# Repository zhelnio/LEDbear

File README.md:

# LEDbear
Just a simple RGB LED toy

**Schematic**

**Board**

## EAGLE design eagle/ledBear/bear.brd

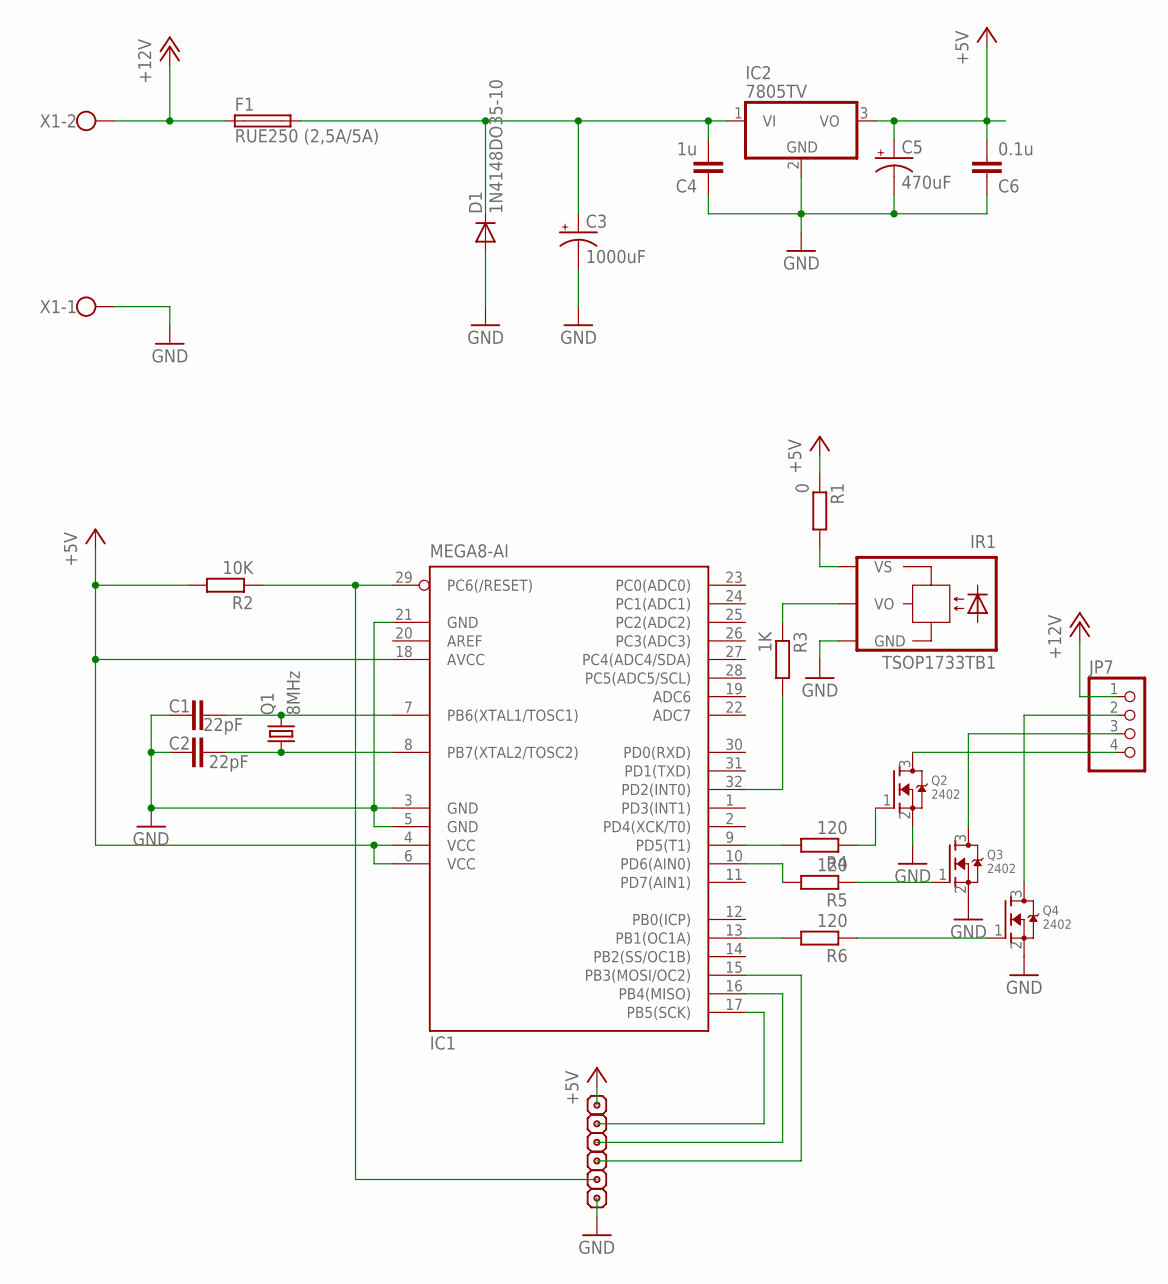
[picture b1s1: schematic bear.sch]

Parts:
C1, C2: 22pF; C1206
C3: 1000uF; E5-10,5
C4: 1u; C1206K
C5: 470uF; E5-8,5
C6: 0.1u; C1206K
D1: 1N4148DO35-10; DO35-10
F1: RUE250 (2,5A/5A); TE5
IC1: MEGA8-AI; TQFP32-08
IC2: 7805TV; TO220V
IR1: TSOP1733TB1; TSOP17_TB1
JP7: PINHD-1X4_2.54; 1X04
JP_5V: PINHD-1X1_2.54; 1X01
JP_GND: PINHD-1X1_2.54; 1X01
JP_MISO: PINHD-1X1_2.54; 1X01
JP_MOSI: PINHD-1X1_2.54; 1X01
JP_RST: PINHD-1X1_2.54; 1X01
JP_SCK: PINHD-1X1_2.54; 1X01
Q1: 8MHz; HC49/S
Q2, Q3, Q4: 2402; SOT23
R1: 0; R1206
R2: 10K; R1206
R3: 1K; R1206
R4, R5, R6: 120; R1206
X1: W237-102

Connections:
+5V: C5.+, C6.2, IC1.4 (VCC), IC1.6 (VCC), IC1.18 (AVCC), IC2.3 (VO), JP_5V.1, R1.1, R2.2
+12V: F1.1, JP7.1, X1.2
GND: C1.1, C2.1, C3.-, C4.1, C5.-, C6.1, D1.A, IC1.3 (GND), IC1.5 (GND), IC1.21 (GND), IC2.2 (GND), IR1.GND, JP_GND.1, Q2.2 (S), Q3.2 (S), Q4.2 (S), X1.1
unnamed: IC1.32 (PD2(INT0)), R3.2
unnamed: IR1.VO, R3.1
unnamed: C3.+, C4.2, D1.C, F1.2, IC2.1 (VI)
unnamed: JP7.4, Q2.3 (D)
unnamed: JP7.3, Q3.3 (D)
unnamed: JP7.2, Q4.3 (D)
unnamed: IC1.9 (PD5(T1)), R4.2
unnamed: Q2.1 (G), R4.1
unnamed: IC1.10 (PD6(AIN0)), R5.2
unnamed: Q3.1 (G), R5.1
unnamed: IC1.13 (PB1(OC1A)), R6.2
unnamed: C1.2, IC1.7 (PB6(XTAL1/TOSC1)), Q1.2
unnamed: IR1.VS, R1.2
unnamed: IC1.17 (PB5(SCK)), JP_SCK.1
unnamed: Q4.1 (G), R6.1
unnamed: IC1.16 (PB4(MISO)), JP_MISO.1
unnamed: IC1.15 (PB3(MOSI/OC2)), JP_MOSI.1
unnamed: C2.2, IC1.8 (PB7(XTAL2/TOSC2)), Q1.1
RESET: IC1.29 (PC6(/RESET)), JP_RST.1, R2.1

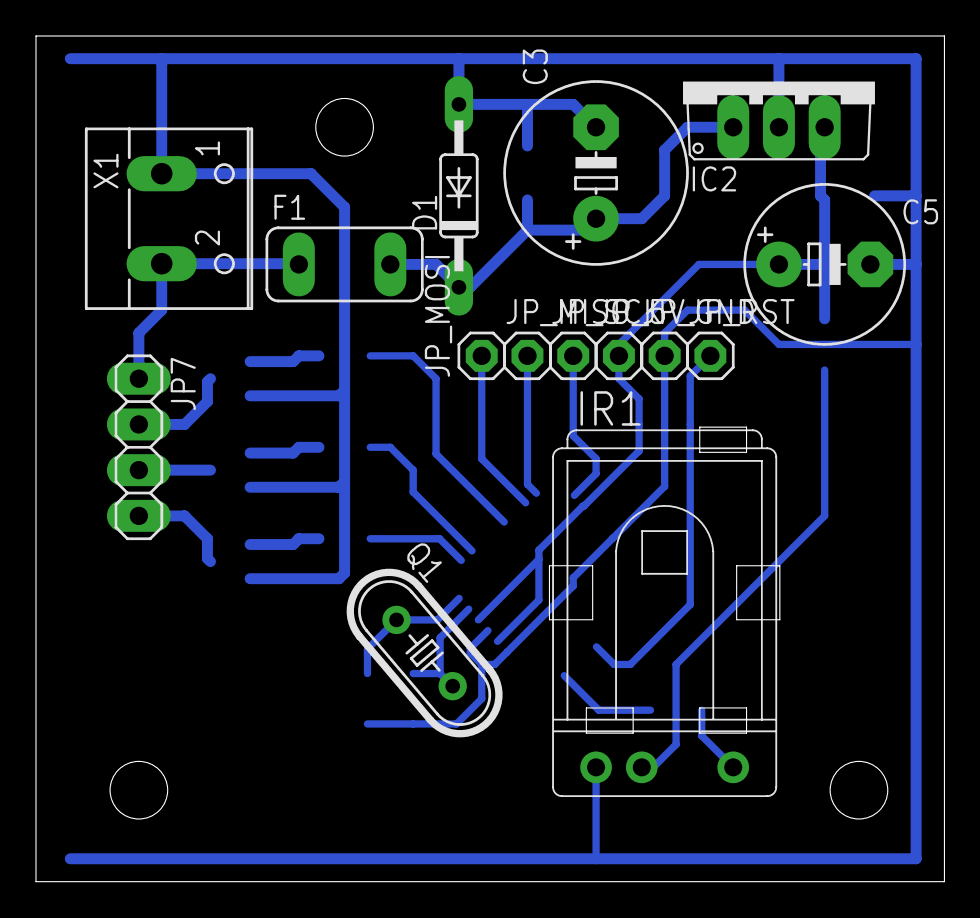
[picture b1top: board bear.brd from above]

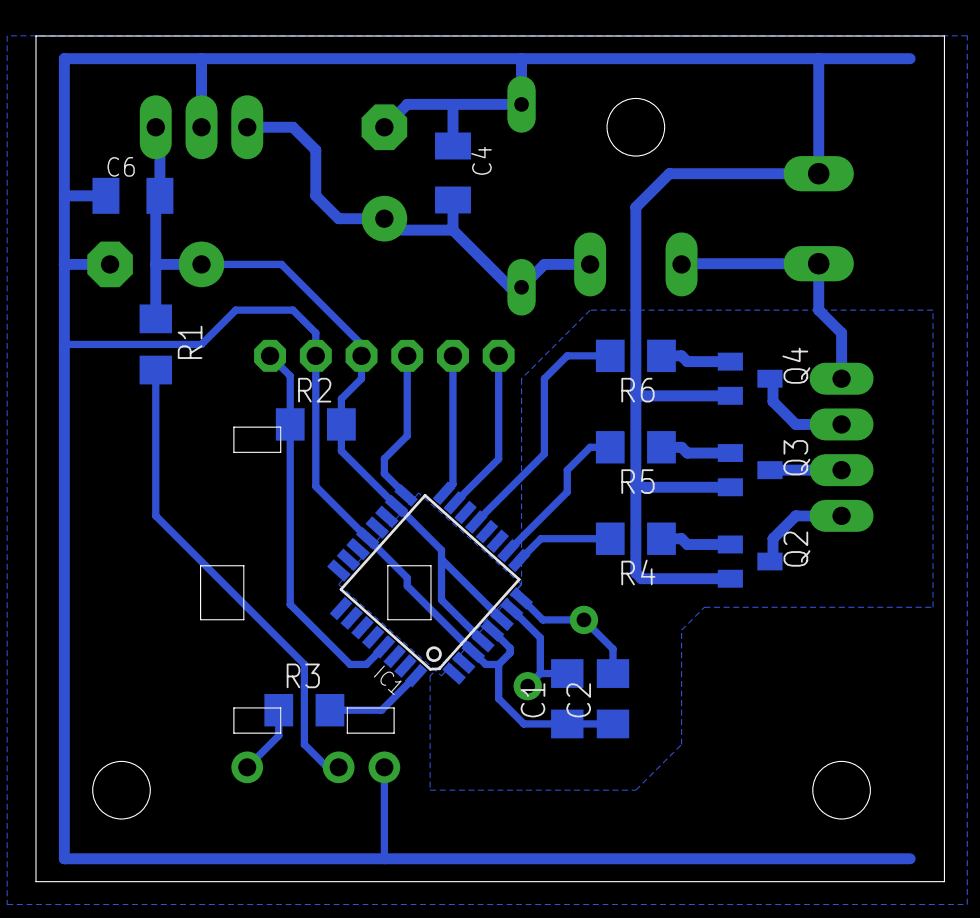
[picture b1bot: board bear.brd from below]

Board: 2 copper layers, 50.5 x 47.0 mm, 29 parts (14 on the bottom side), 22 nets.

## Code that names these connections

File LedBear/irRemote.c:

/*
 * irRemote.c
 *
 * Created: 09.03.2015 11:39:01
 * прошивка для управления RGB светодиодной лентой c IR пульта
 * устройство построено на базе atmega88pa + 8МГц кварц
 * вход: PD2 (INT0) - с ИК-приемника TSOP17
 * выходы ШИМ (RGB): PD6, PD5, PB1
 *
 * модуль декодирования ИК-команд
 */ 

#include <avr/io.h>
#include <avr/interrupt.h>
#include "common.h"

#define FIFO_SIZE	16
uint16_t fifo[FIFO_SIZE];
int8_t fifoIndex = -1;

//поместить принятую команду в очередь на обработку
void putIrCmd(uint16_t data)
{
	if(fifoIndex < FIFO_SIZE - 1)
		fifo[++fifoIndex] = data;
}

//получить команду из очереди принятых команд
uint16_t getIrCmd()
{
	uint16_t result;
	cli();
	if(fifoIndex < 0)
		result = 0;
	else
		result = fifo[fifoIndex--];
	sei();
	return result;
}

//кол-во принятых бит + 1
uint8_t volatile receiveMode = 0;

//обработка полученного бита сигнала
inline void irSignalFront(uint8_t period)
{
	static uint16_t irData = 0;
	
	//получен повтор предыдущей команды
	if(!receiveMode && (period >= 0xE2 && period <= 0xE9))
	{
		putIrCmd(0xFF);
		return;
	}
	
	//получено начало команды 
	if(!receiveMode && period >= 0x5D && period <= 0x70)
	{
		receiveMode = 1;
		irData = 0;
		return;
	}
	
	//получен очередной бит команды
	if(receiveMode)
	{
		irData = irData << 1;
		if(period >= 0x0F && period <= 0x12)
			irData++;
		receiveMode++;
	}
	
	//получен последний бит команды
	if(receiveMode == 33)
	{
		putIrCmd(irData);
		receiveMode = 0;
	}
}

//сброс приема команд 
//вызывается в прерывании при переполнении счетчика таймера
inline void irSignalTimeout(void)
{
	if(receiveMode)
	{
		receiveMode = 0;
		USART_Transmit('\n');
	}
}

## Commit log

2016-08-06 init
2016-08-06 utf8 comments fixed
2016-09-18 github lang change
